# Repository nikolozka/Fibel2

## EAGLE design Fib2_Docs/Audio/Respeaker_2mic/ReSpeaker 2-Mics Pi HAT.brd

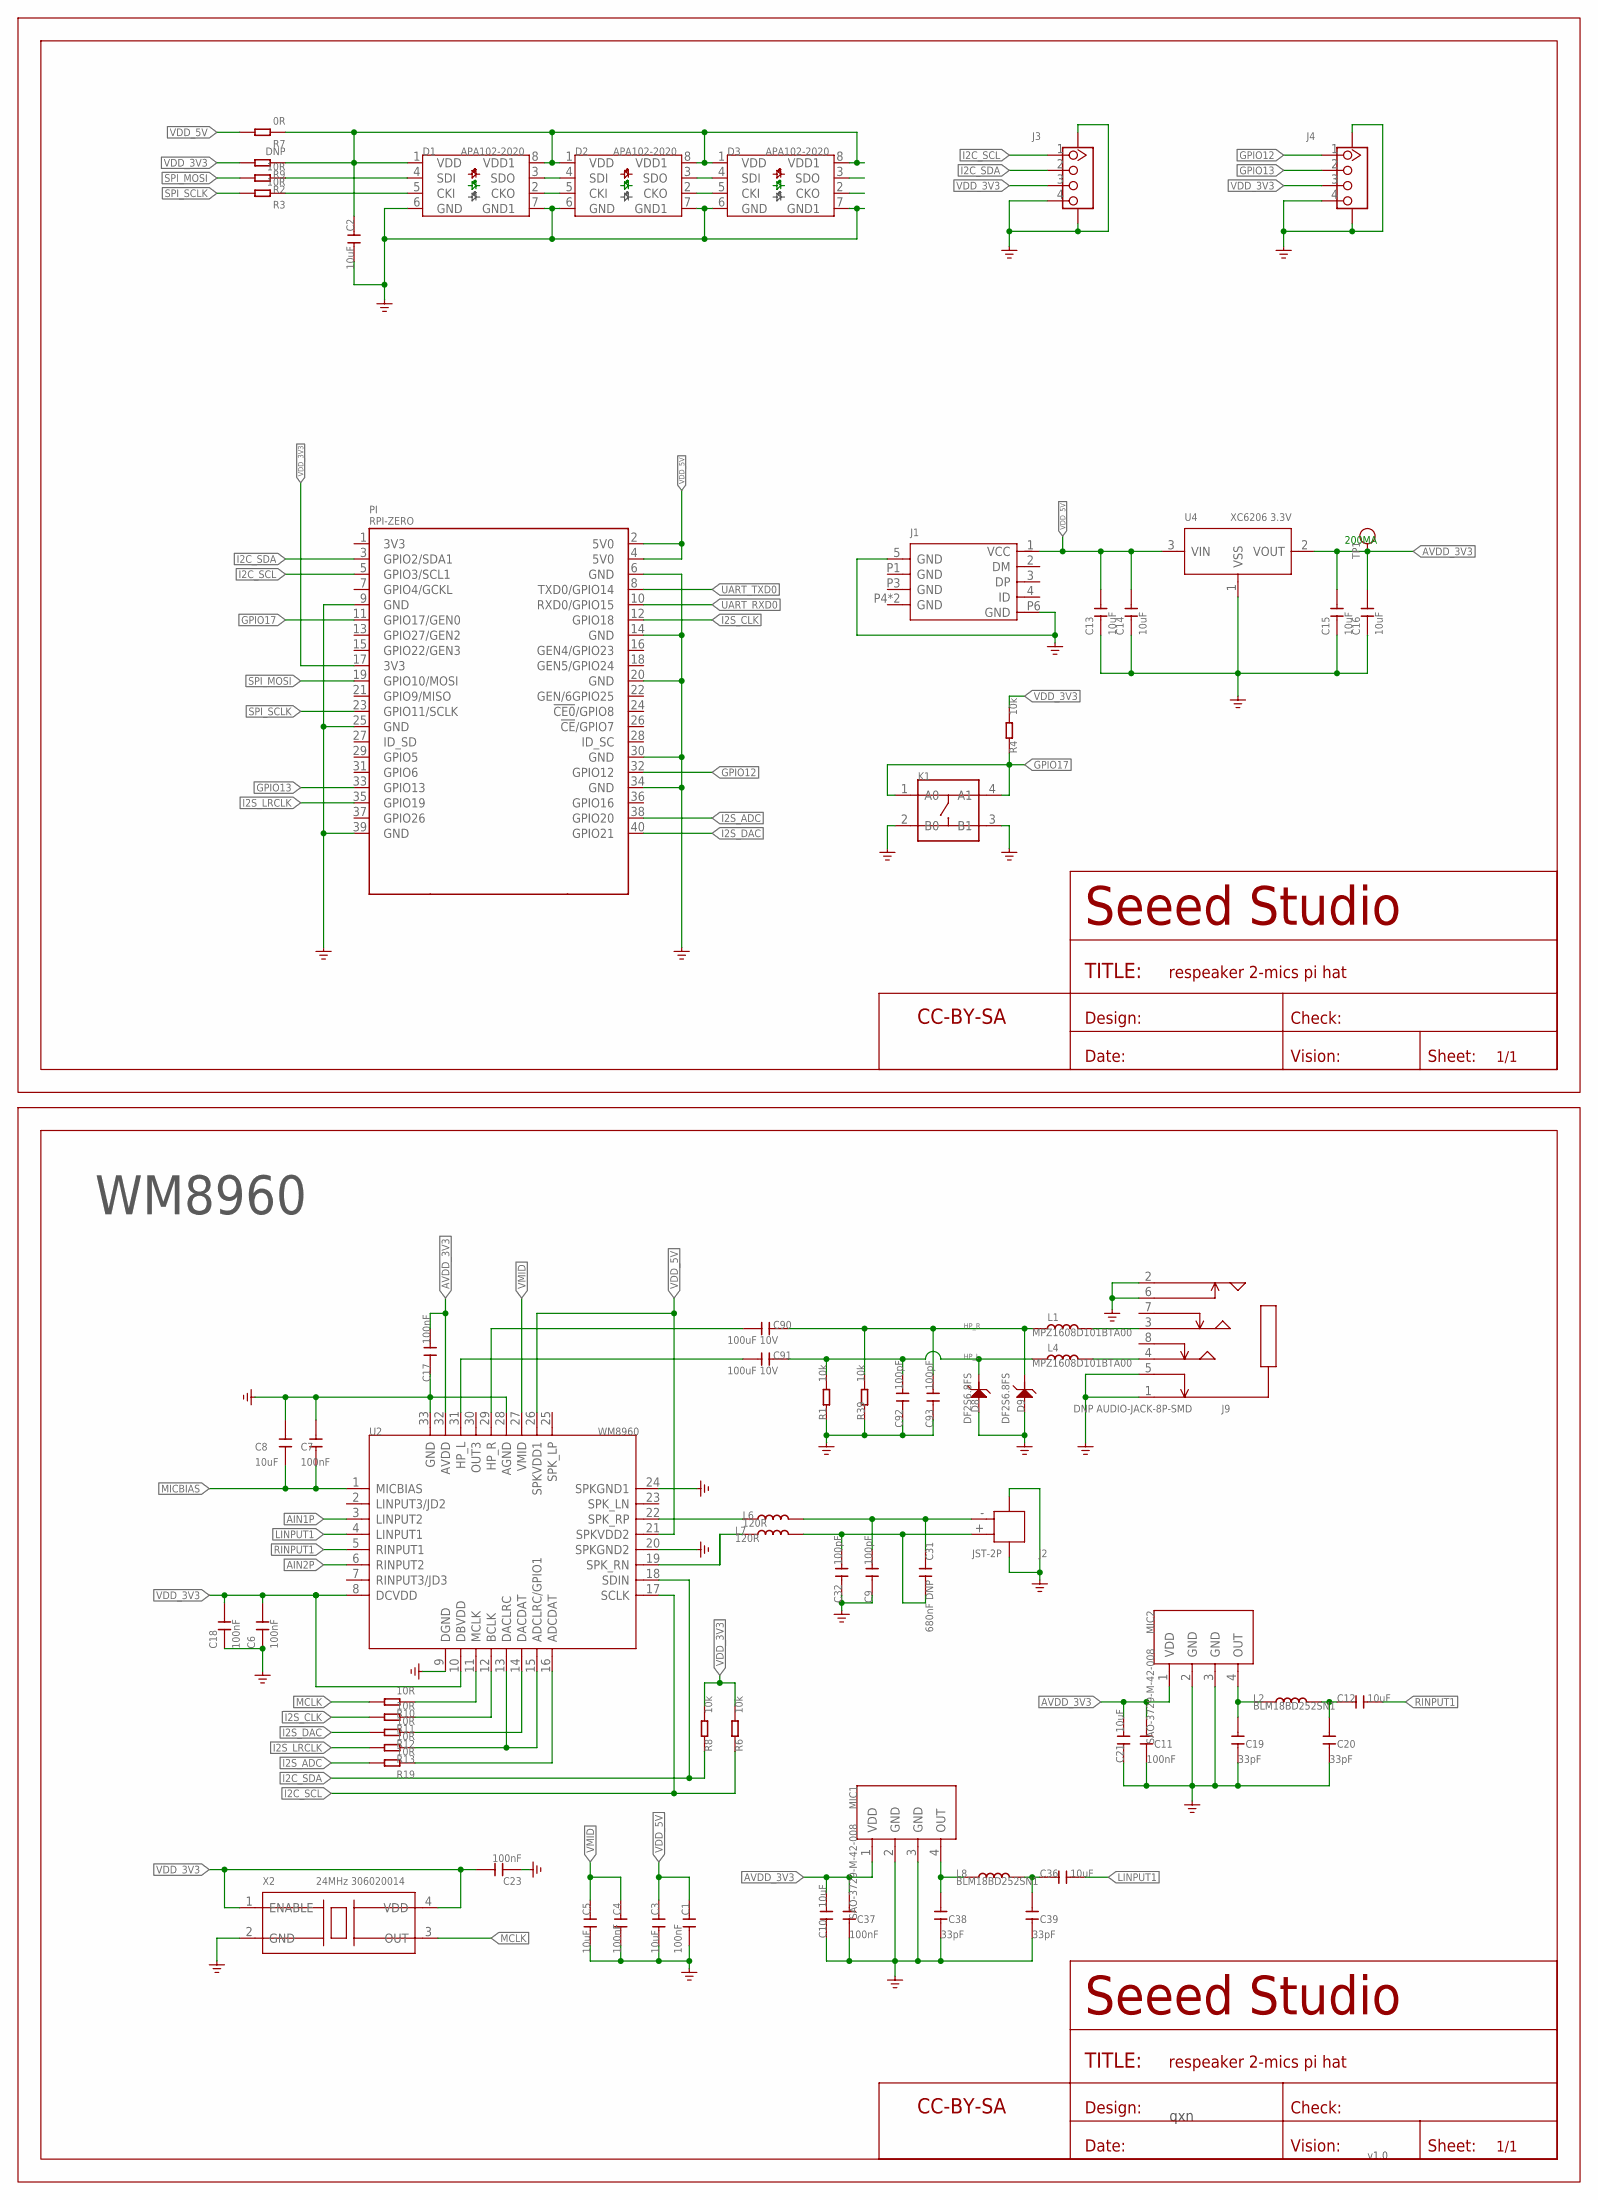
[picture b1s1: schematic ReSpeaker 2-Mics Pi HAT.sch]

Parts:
C1, C4, C6, C7, C11, C17, C18, C23, C37: 100nF; C0402
C2, C3, C5, C8, C10, C12, C13, C14, C15, C16, C21, C36: 10uF; C0603
C9, C32, C92, C93: 100pF; C0402
C19, C20, C38, C39: 33pF; C0402
C31: 680nF DNP; C0402
C90, C91: 100uF 10V; C0805
D1, D2, D3: APA102-2020; RGB2020
D8, D9: DF2S6.8FS; SOD-923
FR1, FR8: SEEEDSTUDIO-OPEN-SCH-FRAME; SEEEDSTUDIO-PCB-FRAME
J1: MICRO-USB5+4P; MICRO-USB5+5P-SMD-0.65-7.2X5.06MM
J2: JST-2P; HW2-SMD-2.0-90D
J3, J4: GROVE-CONNECTOR-SMD'90D'; HW4-SMD-2.0-90D
J9: DNP AUDIO-JACK-8P-SMD; AUDIO8P-SMD-3.5-14.5X6.1X4.0MM
K1: BUTTON-4PDTSM-62K-S-V-T/R(SN431); SW4-SMD-6.0X6.0X5.0MM
L1, L4: MPZ1608D101BTA00; L0603
L2, L8: BLM18BD252SN1; L0603
L6, L7: 120R; L0603
MIC1, MIC2: SAO-3729-M-42-008; MIC4-SMD-3.76X2.95MM
PI: RPI-ZERO; RASPBERRYPI_BASTELSTUBE_V13_RASPI_BOARD_B+_FULL
R1, R4, R6, R8, R39: 10k; R0402
R2, R3, R10, R11, R12, R13, R19: 10R; R0402
R7: 0R; R0402
R9: DNP; R0402
TP1: TEST-POINT-D65/35; TP-D65/35MIL
U2: WM8960; QFN32G-0.5-5X5MM
U4: XC6206 3.3V; SOT-23
X2: 24MHz 306020014; OSC4-SMD-2.5X2.0X0.8MM

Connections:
$123: C90.1, U2.29 (HP_R)
$124: C91.1, U2.31 (HP_L)
AIN1P: U2.3 (LINPUT2)
AIN2P: U2.6 (RINPUT2)
AVDD_3V3: C10.2, C11.2, C15.2, C16.2, C17.2, C21.2, C37.2, MIC1.1 (VDD), MIC2.1 (VDD), TP1.P1, U2.32 (AVDD), U4.2 (VOUT)
GND: C1.1, C2.2, C3.2, C4.1, C5.2, C6.1, C7.2, C8.1, C9.1, C10.1, C11.1, C13.1, C14.1, C15.1, C16.1, C17.1, C18.1, C19.1, C20.1, C21.1, C23.1, C32.1, C37.1, C38.1, C39.1, C92.1, C93.1, D1.6 (GND), D1.7 (GND1), D2.6 (GND), D2.7 (GND1), D3.6 (GND), D3.7 (GND1), D8.2 (1), D9.2 (1), J1.5 (GND), J1.P6 (GND), J2.3, J2.4, J3.4, J3.SS1, J3.SS2, J4.4, J4.SS1, J4.SS2, J9.1, J9.2, J9.5, J9.6, K1.2 (B0), K1.3 (B1), MIC1.2 (GND), MIC1.3 (GND), MIC2.2 (GND), MIC2.3 (GND), PI.6 (GND), PI.9 (GND), PI.14 (GND), PI.20 (GND), PI.25 (GND), PI.30 (GND), PI.34 (GND), PI.39 (GND), R1.1, R39.1, U2.9 (DGND), U2.20 (SPKGND2), U2.24 (SPKGND1), U2.28 (AGND), U2.33 (GND), U4.1 (VSS), X2.2 (GND)
GPIO12: J4.1, PI.32 (GPIO12)
GPIO13: J4.2, PI.33 (GPIO13)
GPIO17: K1.1 (A0), K1.4 (A1), PI.11 (GPIO17/GEN0), R4.1
HP_L: C91.2, C92.2, D8.1 (2), L4.1, R1.2
HP_R: C90.2, C93.2, D9.1 (2), L1.1, R39.2
I2C_SCL: J3.1, PI.5 (GPIO3/SCL1), R6.1, U2.17 (SCLK)
I2C_SDA: J3.2, PI.3 (GPIO2/SDA1), R8.1, U2.18 (SDIN)
I2S_ADC: PI.38 (GPIO20), R19.2
I2S_CLK: PI.12 (GPIO18), R11.2
I2S_DAC: PI.40 (GPIO21), R12.2
I2S_LRCLK: PI.35 (GPIO19), R13.2
LINPUT1: C36.2, U2.4 (LINPUT1)
MCLK: R10.2, X2.3 (OUT)
MICBIAS: C7.1, C8.2, U2.1 (MICBIAS)
unnamed: D1.2 (CKO), D2.5 (CKI)
unnamed: D1.4 (SDI), R2.1
unnamed: C12.1, C20.2, L2.2
unnamed: D1.3 (SDO), D2.4 (SDI)
unnamed: D1.5 (CKI), R3.1
unnamed: C38.2, L8.1, MIC1.4 (OUT)
unnamed: C19.2, L2.1, MIC2.4 (OUT)
unnamed: D2.2 (CKO), D3.5 (CKI)
unnamed: L6.1, U2.22 (SPK_RP)
unnamed: R12.1, U2.14 (DACDAT)
unnamed: D2.3 (SDO), D3.4 (SDI)
unnamed: L7.1, U2.19 (SPK_RN)
unnamed: J9.3, L1.2
unnamed: C36.1, C39.2, L8.2
unnamed: R19.1, U2.16 (ADCDAT)
unnamed: R13.1, U2.13 (DACLRC), U2.15 (ADCLRC/GPIO1)
unnamed: R11.1, U2.12 (BCLK)
unnamed: R10.1, U2.11 (MCLK)
unnamed: C9.2, C31.1, J2.- (2), L6.2
unnamed: C31.2, C32.2, J2.+ (1), L7.2
unnamed: J9.4, L4.2
RINPUT1: C12.2, U2.5 (RINPUT1)
SPI_MOSI: PI.19 (GPIO10/MOSI), R2.2
SPI_SCLK: PI.23 (GPIO11/SCLK), R3.2
UART_RXD0: PI.10 (RXD0/GPIO15)
UART_TXD0: PI.8 (TXD0/GPIO14)
VDD_3V3: C6.2, C18.2, C23.2, J3.3, J4.3, PI.17 (3V3), R4.2, R6.2, R8.2, R9.2, U2.8 (DCVDD), U2.10 (DBVDD), X2.1 (ENABLE), X2.4 (VDD)
VDD_5V: C1.2, C3.1, C13.2, C14.2, J1.1 (VCC), PI.2 (5V0), PI.4 (5V0), R7.2, U2.21 (SPKVDD2), U2.26 (SPKVDD1), U4.3 (VIN)
VDD_LED: C2.1, D1.1 (VDD), D1.8 (VDD1), D2.1 (VDD), D2.8 (VDD1), D3.1 (VDD), D3.8 (VDD1), R7.1, R9.1
VMID: C4.2, C5.1, U2.27 (VMID)

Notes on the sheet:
WM8960
qxn
v1.0
200MA

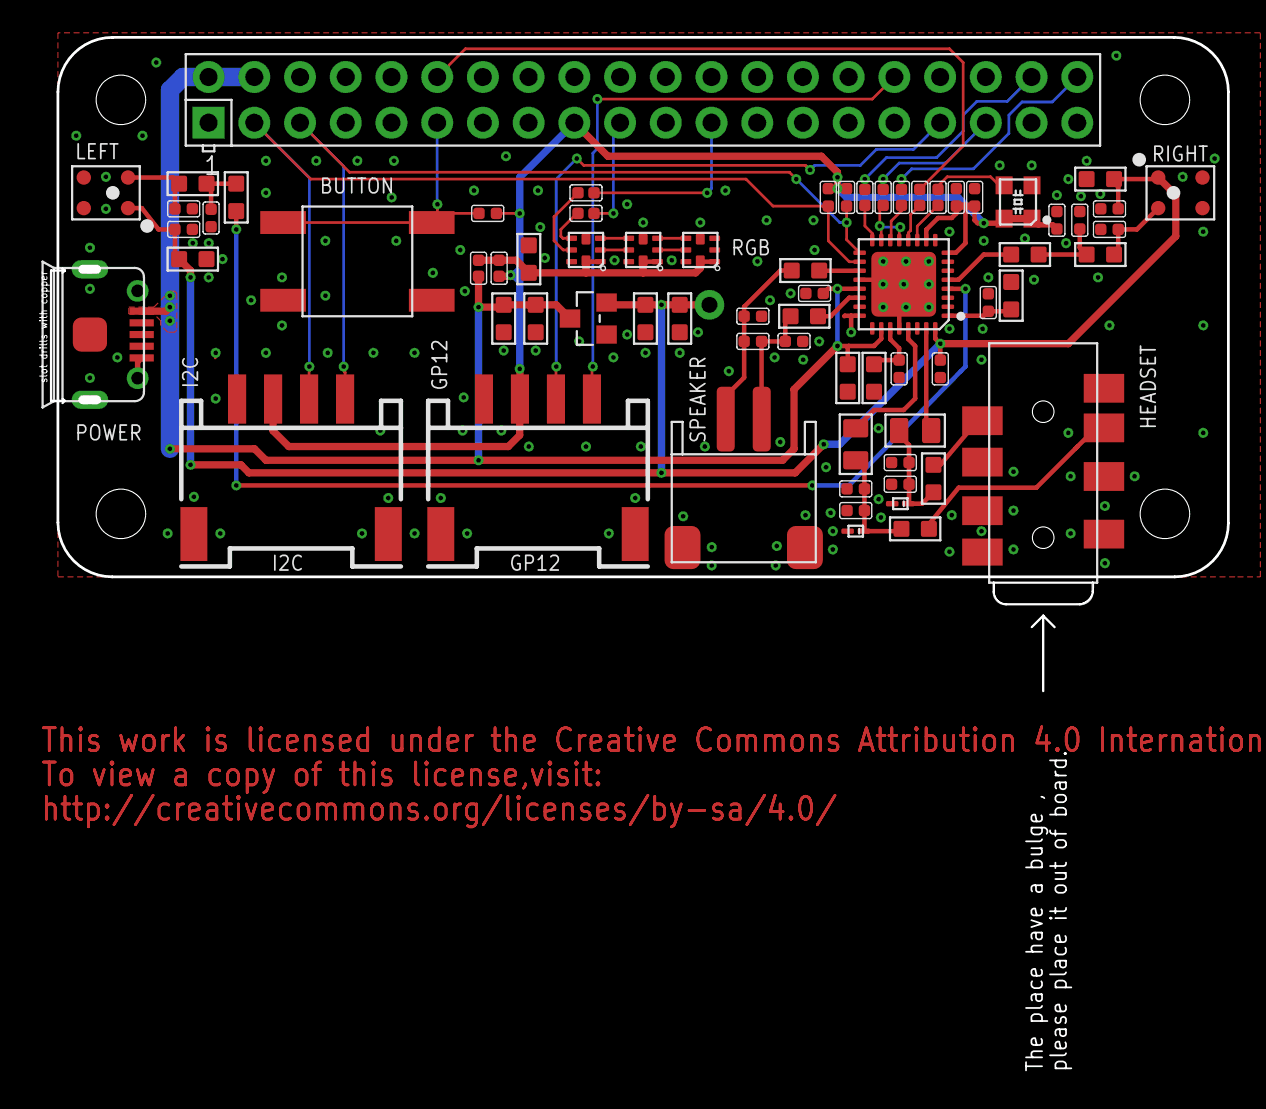
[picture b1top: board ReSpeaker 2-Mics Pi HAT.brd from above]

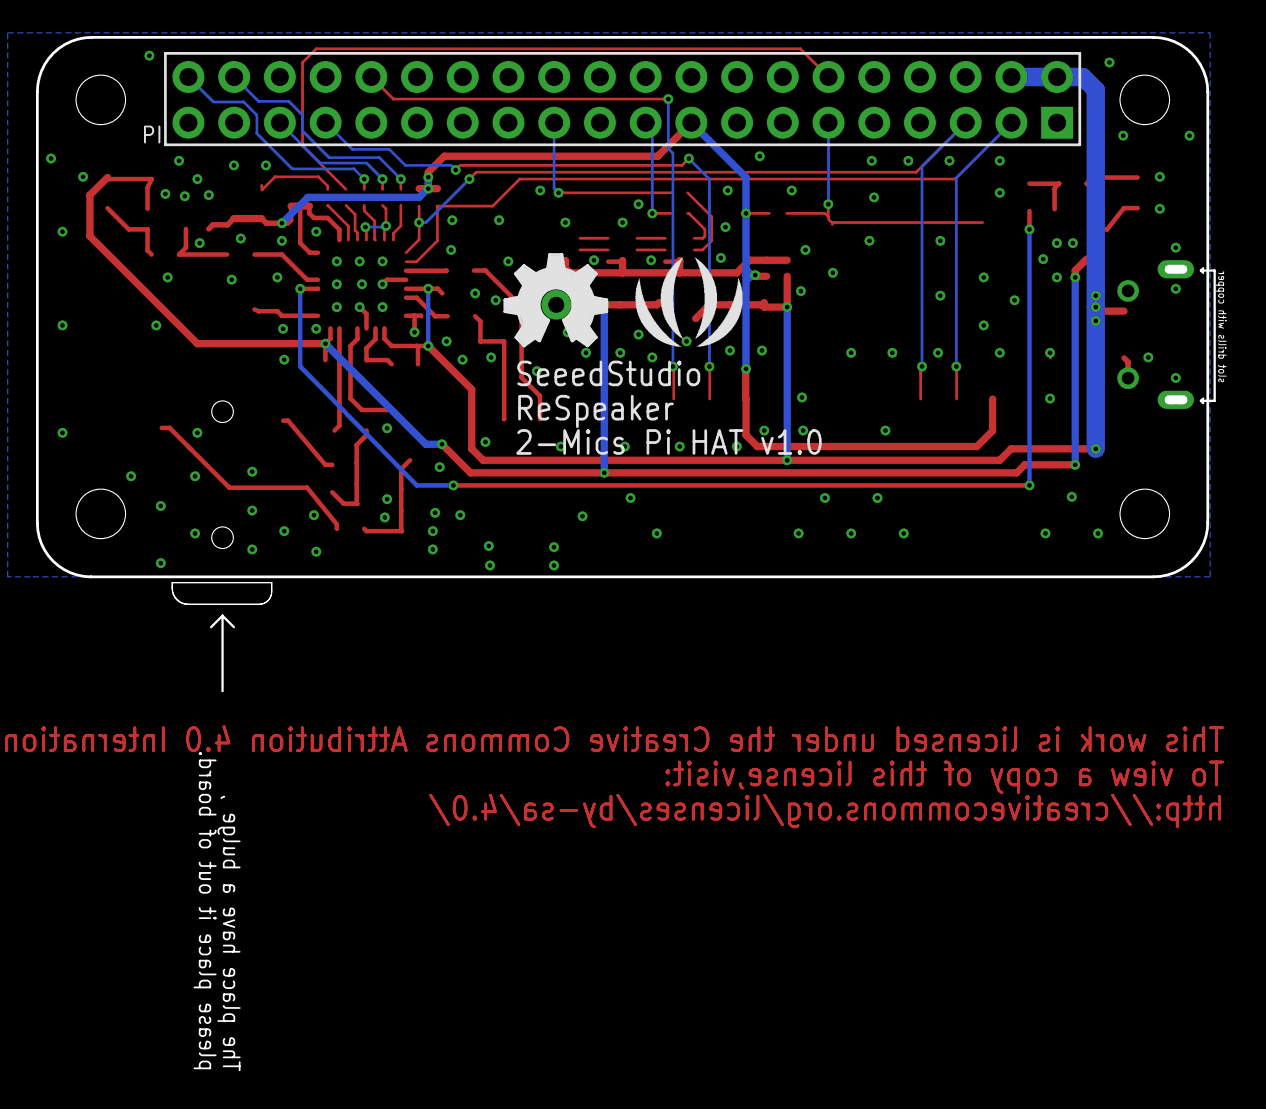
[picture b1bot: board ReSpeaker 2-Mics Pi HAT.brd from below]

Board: 2 copper layers, 65.8 x 57.1 mm, 74 parts (2 on the bottom side), 46 nets.

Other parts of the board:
U$13: SEEED-SILK-280*268MIL
U$22: OSHW_FILLX200_NOTEXT_TNAME

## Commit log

2024-04-29 added documentation for Orin and other ics i'm planning to use, created hierarchy for schematics
2024-05-04 added several ICs, implementted schematics for charger, boost converter and LDOs
2024-05-04 added symbol&footprint for orin/sodimm, added a bunch of specs and docs, partially implemented audio, full steam ahead
2024-05-20 added usb+PD+DP & pcie implementations from antmicro design, added specs for USB components, rethought power+usb arch
2024-05-20 added footprint, symbol and model for TPS65987
2024-05-29 added nets for 40 pin headers (epd & rpi header) connected some of the nets i'm reeusing
2024-05-29 added net labels for pcie (m&e key), reusing a lot of blocks from antmicro
2024-06-05 continuing schematic work for pcie and other high speed interfaces
2024-06-05 renamed /Fib2_Docs/AUX to Others because windows is being a lil bitch
2024-06-17 restructured EPD side of things, replaced rp2040 with esp32 s3 because of it's LCD controller, USB, LP WIFI_BT & EPDiy compat, repurposed USB0 for ESP interfacing, added e-ink pmic
2024-06-19 added notest regarding the audio codec
2024-06-19 added buck converter, refactoored peripherals and updated gpio/SPI/i2c mapping
2024-06-21 partially implemented E-INK PMIC
2024-06-21 added decoupling and inductors for EPD PMIC
2024-06-22 added connections to ESP32 S3, most oof EPD stuff that we're gooing to use is included
2024-06-23 refactored PCIe pages
2024-06-25 added some missing footprints, stared working ono power-on and sequencing
2024-06-29 started arranging the components on the board, added some more missing footprints. starting to think about the overall distribution of parts
2024-06-30 started routing the SODIMM, updated connector footprint, started arranging component into sub-areas
2024-06-30 did a ton of routing and modeling for SOM, USB, DP & Charging/Power, things starting to take shape
2024-07-02 did some work on the ports and layout
2024-07-05 implemented most of USB and Power Supplies
2024-07-07 did a big portion of pcie, optimized placement of components and subsections. power, usb and charging is largely done. still need to do length matching though. will need to take a second look at sche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
2024-07-07 further optimized placement, finished most of buck array, expanded pcie, added tons of missing footprints, diff pair spacing optimization
2024-07-08 90 percent done with routing. need to go over all schematic pages, double check everything thoroughly, do lengthmatching add any missing footprints, take care of startup, ferrites, audio, eink connec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
2024-07-11 replaced 1v8 buck with ldo, added startup circuit, added footprints for eink connectors
2024-07-12 added all missing footprints, fixed library & footprint links, did layout out 99% of components, all that's left is rtc(?), peripherals, routing & lengthmatching and final sanity checks
2024-07-12 removed redundant schematic files
2024-07-12 added gitignore
2024-07-12 added lck file to gitignore
2024-07-14 did length tuning, routing of final submodules and most of power routing
2024-07-14 added port expander and level shifters, routed peripherals fixed most drc errors, assigned gpios etc.
2024-07-16 routed epd displays, added testpoints and all the little checks and fixe, (regrettably) removed the i80 connector, 99% there, need to double check some things add peripheral connectors, shared-ish st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
2024-07-16 finished routing, sanity check and prep fabrication files next
2024-07-18 added second i2c, modified 40 pin headers
2024-07-19 adde testpoints, fixed power supplies, ready to order
2024-07-19 added gerbers

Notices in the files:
parts and their libraries:
moudle-new: This work is licensed under the Creative Commons Attribution 4.0 International License.
To view a copy of this license,visit:
http://creativecommons.org/licenses/by-sa/4.0
moudle-new: CC-BY-SA
